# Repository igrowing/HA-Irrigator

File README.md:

# HA-Irrigator

## What is it?

An intuitive and human-friendly irrigation controller: 11 sprinkler zones + a shared pump, driven by a rotary-encoder + OLED local UI and a full MQTT API for Home Assistant integration. 

### Top differentiation points
- Human-friendly intuitive control on device and via Home Assistant.
- Flexible watering control — your command is never lost, your garden is never dry.
- Automatic watering adjustment based on the weather. Yes, it saves water when it rains!
- 110-240VAC pump control directly from the device, no extra contactors or relays.
- External antenna mount for placement wherever you want.
- Malfunction detection for the pump and valves: it protects your garden and your pocket from drying out.
- No battery! No chemical leaks, no device damage.
- Optional Home Assistant integration — works out of the box. It gives you:
  - Human-readable names for the irrigation zones.
  - Irrigation logging.
  - Remote control and status review.
  - Comfortable schedule building and editing.

## Why HA-Irrigator?

HA-Irrigator fixes the traditional shortcomings of industrial watering control systems.

| Trouble | Solution |
|---|---|
| 1.5V or 9V battery - the settings, the schedule, and the clock are backed up with regular batteries. You never know when the battery will die and leak into the device. And when the battery is dead and the mains power fails, you lose the whole schedule. This forces you to stand again in front of your irrigator, recall what the program was, and configure everything from scratch. | We keep all the settings and schedule in non-volatile memory. It does not require a battery. The clock runs on a battery that lasts 10 years and NEVER leaks. Your device is a safe investment, and your precious time is saved: no more re-configurations. |
| You cannot really manage any irrigator without reading manuals and standing in front of the device for a long time. | HA-Irrigator is intuitive! It requires zero configuration in front of the device. And when you approach it for manual commands, it helps you with on-screen hints. |
| Some irrigators have built-in or added Wi-Fi modules. But the Wi-Fi has a hidden antenna. This forces the owner to place the irrigator somewhere with decent Wi-Fi signal reception. | HA-Irrigator has an external SMA antenna connector. The owner is free to connect the antenna directly to the irrigator, or relocate it using a long enough coaxial cable to place the antenna in an area with good signal reception. |
| You never know if an industrial irrigator followed your program. You only find out once your garden dries up and dies. | HA-Irrigator gives you precise logging of what happened and when. |
| You must adjust the watering seasonally. If you forget, your garden suffers from lack of water, or your wallet suffers from excess spending. | HA-Irrigator has weather awareness. You just set a base watering amount per zone, and from there the system takes control: when it's too dry, watering is increased proportionally. When it rains, you save the water (and the cost). |
| Industrial irrigators force you to approach them and stand in front of the device to see its status or configure its programs. | We give you the power to see and change everything from your computer or mobile phone. More than that, it can be integrated with your smart home. So your home can configure the irrigator if you wish. |
| Traditionally, irrigators have at least 4 buttons and/or a dial with weird labels. Confusing and not intuitive. | This device has 1 (only one) knob. You rotate and push it like the volume knob in your car. And it helps you with navigation on the screen if you get lost. |
| Manual control of a normal irrigator is timed out. It takes your command after 10-30 seconds. | HA-Irrigator does not waste your time. Your command is executed immediately. If you don't appreciate half a minute of your life wasted, then this feature is meaningless :) |
| Usually, if you set a different manual command on a normal irrigator, the current watering is aborted. | HA-Irrigator assumes that every command is important. It puts all your commands in line. When the command's turn arrives, it is executed. Just fire and forget. |
| Industrial irrigators have a limit on programs, and a limit on entries per program. Why? | We hate limits. Feel free to build the weirdest schedule ever, we accommodate that! |
| Even if an off-the-shelf irrigator provides "smart" access and features, it only works if you're close to it (over Bluetooth) or over the vendor's remote server (forget your privacy!) | HA-Irrigator is your private system: you run it, access it as you want, configure it — you're in control! |

## Feature overview

- **11 independently-named sprinkler zones** plus pump-only runs, with the pump always
  pre-started ~500ms before a valve opens and kept on for a 60s graceful-shutdown window after a
  valve closes (protects the pump from rapid-cycle wear) — if another watering is queued up, it
  hands off to the still-running pump immediately instead of waiting out that window. Each zone
  can also be individually disabled (`settings.json`'s `zone_names.<n>.enabled`) to exclude it
  from scheduled, manual, and MQTT-triggered watering alike — an MQTT `cmd/run` against a disabled
  zone is rejected with a `/alert` instead of running, and the local UI's manual zone picker (see
  below) skips disabled zones entirely so they can't be dialed up in the first place.
- **Weekly schedule** (`schedule.json`, almost endless count of records) with a per-zone watering-percentage
  multiplier, a pause/rain-skip mechanism, and a 15-deep queue so overlapping or MQTT-triggered
  runs during an active watering don't get lost — they queue and run in order, back-to-back on
  the same pump cycle whenever the pump is still spinning down from the previous one.
- **Local UI**: 2.4-inch OLED display and knob, auto-dimming after 20s of inactivity, full menu for stopping, viewing/adjusting the schedule, and settings.
- **MQTT**: Key feature, allowing you to connect HA-Irrigator to practically any smart home system. Provides status/availability reporting (Home-Assistant-compatible LWT), remote run/stop/schedule control, current-fault alerting, OTA updates, calibration, and file backup.
- **Captive-portal setup**: first boot (or after a factory-reset-style config wipe) serves a
  Wi-Fi AP with a setup page; it tests both Wi-Fi *and* MQTT connectivity before committing the new config, and rolls back to AP mode if either fails.
- **DS3231-backed clock** with NTP sync, a timezone auto-detected from the device's location (no
  dropdown to pick), and automatic EU DST switching (last Sunday of March/October, 01:00 UTC).
- **Weather-based auto-adjustment**: once the device knows its location (auto-detected via
  ip-api.com, no setup needed), it fetches a forecast (Open-Meteo, with a WeatherAPI.com fallback)
  a few hours ahead of your first scheduled watering each day, skips the day's scheduled runs
  entirely when meaningful rain is forecast, and otherwise nudges the watering percentage up in
  hot weather / down after recent rain — all within a configurable lower/upper bound. See
  [docs/usage_irrigator.md](docs/usage_irrigator.md) and [docs/technical.md](docs/technical.md).
  The result of auto-adjustment work is shown on the chart below:

    * Rain reduces the waterin time/amount. The amount of rain in last 5 days has the same impact as forecasted amount of rain with probability higher than 70%.
    * You can adjust the probability of rain to be taken into account and the lower threshold to skip watering - default 40%.
- **Name your zones**. Numbers are nice, but words work better for people.
- Configurable time for testing of all zones.

## Device

## Screenshots

### Status and manual control

### Settings

### Schedule

See more screenshots in [User guide for HA](docs/usage_homeassistant.md).

## Useful (further reading)
- [User guide of the HA-Irrigator](docs/usage_irrigator.md), including installation instructions.
- [User-guide for HA integration](docs/integration.md).
- [User guide for HA](docs/usage_homeassistant.md).
- [Technical explanations](docs/technical.md) (for geeks only).
- [OTA firmware upgrade](docs/ota.md) (for makers only).
- [Crash dumps](docs/coredump.md) — retrieving and decoding a panic dump over MQTT (for makers only).
- [Hardware](hardware/readme.md).

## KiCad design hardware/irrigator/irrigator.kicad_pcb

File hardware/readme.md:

## Electronics

[Schematics](schematics.pdf)

ESP32 DevKit Pinout:

### Parts

| Ref             | Part                              | Description                                                                          | Qty |
|-----------------|------------------------------------|---------------------------------------------------------------------------------------|-----|
| U1              | ESP32-WROOM-32U dev kit           | Main microcontroller board                                                            | 1   |
| U2              | DS3231M                           | I2C real-time clock module                                                            | 1   |
| BT1             | CR2032                            | 3V coin cell, RTC backup battery                                                       | 1   |
| J6              | SSD1309 OLED 2.4"                     | I2C OLED display module                                                               | 1   |
| SW1             | Rotary encoder w/ push-button     | User input for menu navigation                                                         | 1   |
| U4              | AC-DC PSU, 230VAC → 5VDC 3A       | Powers ESP32, logic and display                                                        | 1   |
| —               | Transformer, 230VAC → 24VAC       | Powers valves relay coils (Eco wiring only)                                            | 1   |
| L1, L2          | HWCT-5A/5mV current clamp sensor  | Non-invasive AC current sensing — L1 on 24VAC (valves), L2 on 230VAC (pump)            | 2   |
| J1–J3           | 4-channel 5V relay module         | 12 relays total: 11 valves + 1 pump ("Relays group 1/2/3")                             | 3   |
| D1–D24          | 1N4003 diode                      | Only for non-opto-isolated ("red") relay modules; use a jumper instead on opto ("blue") modules | 24 (optional) |
| D25             | Blue LED, 5mm                     | Status/fault indicator                                                                | 1   |
| R1–R3, R8, R9, R12–R25 | 10kΩ resistor               | Pull-ups: rotary encoder, current sensors, relay inputs                               | 19  |
| R4, R5, R7, R11 | 100Ω resistor                     | Rotary encoder and current sensor signal conditioning                                  | 4   |
| R6, R10         | 1kΩ resistor                      | Current sensor burden resistor (24VAC / 230VAC)                                        | 2   |
| R26             | 30Ω resistor                      | LED current limiting                                                                   | 1   |
| C1, C4, C5      | 100nF capacitor                   | Rotary encoder debounce                                                                | 3   |
| C6, C7          | 10nF capacitor                    | Rotary encoder debounce                                                                | 2   |
| C2, C10         | 100µF 10V capacitor               | Decoupling (ESP32, OLED)                                                               | 2   |
| C8, C9          | 10µF 10V capacitor                | Current sensor filtering (24VAC / 230VAC)                                              | 2   |
| C3              | 470µF 16V capacitor               | PSU output smoothing                                                                   | 1   |
| J4, J5          | 19-pin headers                    | ESP32 devkit sockets                                                                   | 2   |
| J7–J9           | Screw terminal / JST connectors   | Mains AC in, PSU AC in, PSU DC out wiring                                              | 3   |

### About the relay modules
There are 2 types of "cheap" 4x relay modules on the market:

| PCB color | Blue | Red |
|--|--|--|
| Connectivity | 0.1" header | Terminal blocks |
| Active | Low | Configurable with jumper High/Low |
| Dimensions | Slightly larger | Slightly smaller |
| Optocopler | Less sensitive | Very sensitive |
| Assembly | simple | requires voltage drop diodes |

Red boards require volrage drop diodes to set the optocouplers in high state (non-active) when the MCU is high. All boards require pullups.

## Mechanical design

- [Base](irrigator%20box.stl)
- [Lid](irrigator%20lid.stl)

## Installation wiring

In industrial irrigators the 24VAC transformer is often integrated into the irrigator. This reduces the customer flexibility where to mount the irrigator and what type of valves to use. Also, always connected transformer has parasitic current consumptions which hits customer wallet and hurts to the ecology. Our irrigator allows using any 24VAC transformer. It can be mounted on DIN rail or standalone. And it can be driven together with pump, i.e. it is not always connected to mains. This means **more flexibility, less electricilty bill, and less environment impact**.

## Antenna

Wi-Fi reception is critical only for automatic watering adjustment by the weather and for Home Assistant integration. HA-Irrigator can work without Wi-Fi too.

However, for the sake of installation flexibility, the antenna has separate SMA connector. This allows to install the irrigator practically in any place and run the low-attentuating coaxial cable (type of LMR-240 or HF-240) for up to 10 meters. The antenna then, can be placed in the area with good Wi-Fi signal when the irrigator itself can be even in concrete bunker.

### Simple

### Eco

## Current sensing

There are only 2 current sensors in the irrigator:
- For the pump, 220-240VAC, high current up to 12A.
- For valves, 24VAC, sub-amper current, typically 250mA.

The current measurement is not mandatory for the irrigator functionality. However, it can be useful to detect overcurrent and under current events:
- Overcurrent:
  - Pump blocked.
  - Valve wiring short circuit.
- Undercurrent: circuit discontinuity resulting non-fucntioning pump and/or valve.

In both cases there is a risk of over-drying of your garden.

One valve current sensor is enough for 11 valves because valves are never opened together, only 1 zone works at every given moment. So it is easy to correlate which valve is malfunctioning.

The current sensing becomes functional only after [current sensor calibration](../docs/usage_irrigator.md#current-sensor-calibration-explained).

### Current sensor sensitivty

The schematics is built to provide the follwing current sensitivity:
| Sensor  | Sensitivity, mV/mA | Sensitivity, mV/A | Saturation (ceiling), A |
|--|--|--|--|
| Valve | 0.82 | 820 | 1.4 |
| Pump | 0.047| 47 | 24.5 |

This means, having `CURRENT_CALIBRATION_MIN_BASE_LEVEL = 30` will fail the calibration of valve which consumes less than 36 mA and the pump that draws less than 640 mA.

## Water flow sensing

### Flow meter: TUF-2000M

An ultrasonic clamp-on flow meter — no pipe-cutting install, reads flow rate and totalized volume over Modbus RTU on RS-485. It also carries its own onboard relay (OCT), configurable locally on the meter to trip on a flow-rate or totalizer threshold — that relay is meant to drive the shut-off valve directly as a hardware failsafe (see below), independent of the ESP32/Wi-Fi being alive.

### Flow meter settings (set on the meter's keypad)

The firmware talks Modbus RTU to slave 1 at 9600 8N1 (see `FLOW_METER_*` in [board_config.h](../include/board_config.h)). The meter must be configured to match, or it stays silent and every request times out (`/cmd/meter` shows `"error": "no valid reading yet"` with `last_modbus_error_text: "Timeout"`).

| Menu | Setting | Required value | Note |
|--|--|--|--|
| M11 | Pipe outer diameter | 44 | Measure yours |
| M12 | Pipe thickness | 9 | Measure yours |
| M14 | Pipe material | 9 (other)| For plastic green pipes |
| M15 | Sound speed in pipe material | 2650 | Not needed to change is non-"other" known pipe material is used |
| M16 | Pipe liner | No Liner | Or select needed liner |
| M18 | Pipe inner diameter |  | Just see that meter calculated your pipe correctly, having pipe OD and thickness (M11, M12) |
| M20 | Liquid type | 0 (water) |  |
| M23 | Transducer type | 19 (TS-2) | Choose your transducer type |
| M24 | Transducer mounting | V or W | Choose what suits better your pipe. For very small pipes W works better. For 1" and up OD the V is good enough |
| M25 | Distance between transducers |  | See for easy of adjustment |
| M63 | Communication protocol | **MODBUS RTU** | Factory default is MODBUS ASCII, which ignores RTU frames completely. Forgetting this was the cause of the first bring-up timeout. |
| M62 | RS-232/RS-485 setup | 9600 baud, parity none, 8 data bits, 1 stop bit | Factory default. Any other parity makes the meter drop every frame silently. |
| M46 | Network address (ID) | 1 | Must equal `FLOW_METER_MODBUS_SLAVE_ID`. |
| M26 | Save settings (Solidify) | run after changing the above | Settings live in RAM until stored. Without this step they revert on the next power cycle (manual, page 4). |

#### Placing and adjustment of transducers
1. Decide the water direction. Put the "Up" transducer on a side from where the water runs. Put the "Down" transducer on a side where the water runs.
2. Use provided with the meter silicon-like tighthening cream between the transducer and the pipe to make air-less tight placement.
3. Using menu M90 move the transducers slightly around the calculated distance from M25 to read on the display Q value between 60 and 90. More is better. After every slight position change let the meter 3-5 seconds to show you the new Q value. When you reached best possible Q, tighten the transducers with provided rings.

#### Diagnosing a silent bus
Menu M49 on the meter displays the raw bytes it receives on the serial port. If bytes show up every couple of seconds, wiring and converter are fine and the fault is in M63/M62/M46. If M49 stays empty, look at the physical link (A/B, termination, converter). On the converter, the R LED blinks for each request coming from the ESP32 and the T LED blinks for each reply going back to it.

#### Meter adjustment
Meter might count water flow even on still water. And it may count the flow wrongly.

1. To set 0 liquid flow, use menu M42. Activating it, wait 30 seconds: do not touch the meter and make 100% sure the water is NOT running.
2. To calibrate the water flow measurement use menu M45. The scale factor is expected/actual.

### RS-485 GPIOs

Every strapping-safe, output-capable GPIO is already claimed by zones/pump/LED/rotary/ADC/I2C (see [board_config.h](../include/board_config.h)), and GPIO0/1/3 are off-limits (factory-reset button, and `Serial`/flashing). That leaves only GPIO2 and GPIO12 — both ESP32 boot-strapping pins:

| Signal | PIN |
|--|--|
| ESP32 TX → converter RXD | 2 | 
| ESP32 RX ← converter TXD | 36 | 
| DE/RE | — (unused/automatic) | 
| GND | GND | 
| VIN | 3V3 |

### RS-485 converter: Waveshare TTL TO RS485 (C)

Picked over a plain MAX485-style breakout for two reasons:
- **Galvanic isolation.** This cable run parallels mains wiring through the garage; the module isolates the RS-485 bus side (both power and signal, via an onboard isolated DC-DC plus a digital isolator) from the ESP32's own logic and ground, so an induced spike on the bus has no metallic path to the MCU even if it gets past the onboard TVS clamp first.
- **Automatic direction switching**, built into the chip — no DE/RE control needed, so the link only spends the 2 GPIOs above instead of 3.

Also has onboard 120Ω termination (enabled by soldering a jumper) and 200W surge / 6kV ESD protection on the bus side. TTL-side pinout: VCC / TXD / RXD / GND, wired to the ESP32's 3.3V / GPIO36 / GPIO2 / GND (crossed: the converter's RXD receives what the ESP32 transmits on GPIO2, and its TXD feeds GPIO36); RS-485 side: A+ / B- / PE.

### Wiring the RS-485 cable

- Shielded twisted pair for A/B.
- Land the shield on the converter's **PE** terminal, at the ESP32 end only — don't also ground it at the flow meter end (that turns the shield into a ground-loop path), and don't bridge PE to the TTL-side GND (that defeats the isolation).
- No common GND wire: the meter's RS-485 port is itself isolated, and its GND terminal is only the transducer ground ("NOT for power and AO and RS485", manual page 8). Two isolated ports need only the A/B pair; this link works that way.

### Why the 120Ω terminator matters

RS-485 is a shared differential line; an un-terminated cable end reflects a fast signal edge back down the wire instead of absorbing it, corrupting bytes — worse at higher baud rates or longer runs. A 120Ω resistor at each of the two *physical ends* of the bus (matched to the cable's characteristic impedance) soaks up the edge instead of reflecting it. Enable it only at the two endpoints, never at an intermediate device on a multi-drop run — extra resistors along the way just overload the driver and attenuate the signal for everyone.

### Room for more RS-485 devices later

RS-485/Modbus is multi-drop: a shut-off valve controller or any other Modbus RTU device can join the same A/B pair later with its own slave ID — no extra ESP32 pins or a second converter needed, they all share this one bus.

### Shut-off valve strategy

Prefer the TUF-2000M's own relay, configured locally (flow-rate or totalizer threshold), as the failsafe that closes a master shut-off valve even when the ESP32 or Wi-Fi is down — the same "don't trust the network for safety-critical stuff" principle the current-sensing overcurrent checks already follow. Poll flow readings over Modbus in firmware as well, for HA reporting/logging and for schedule-aware logic the meter alone can't know (e.g. unusually high volume mid-cycle for whichever zone is currently running).

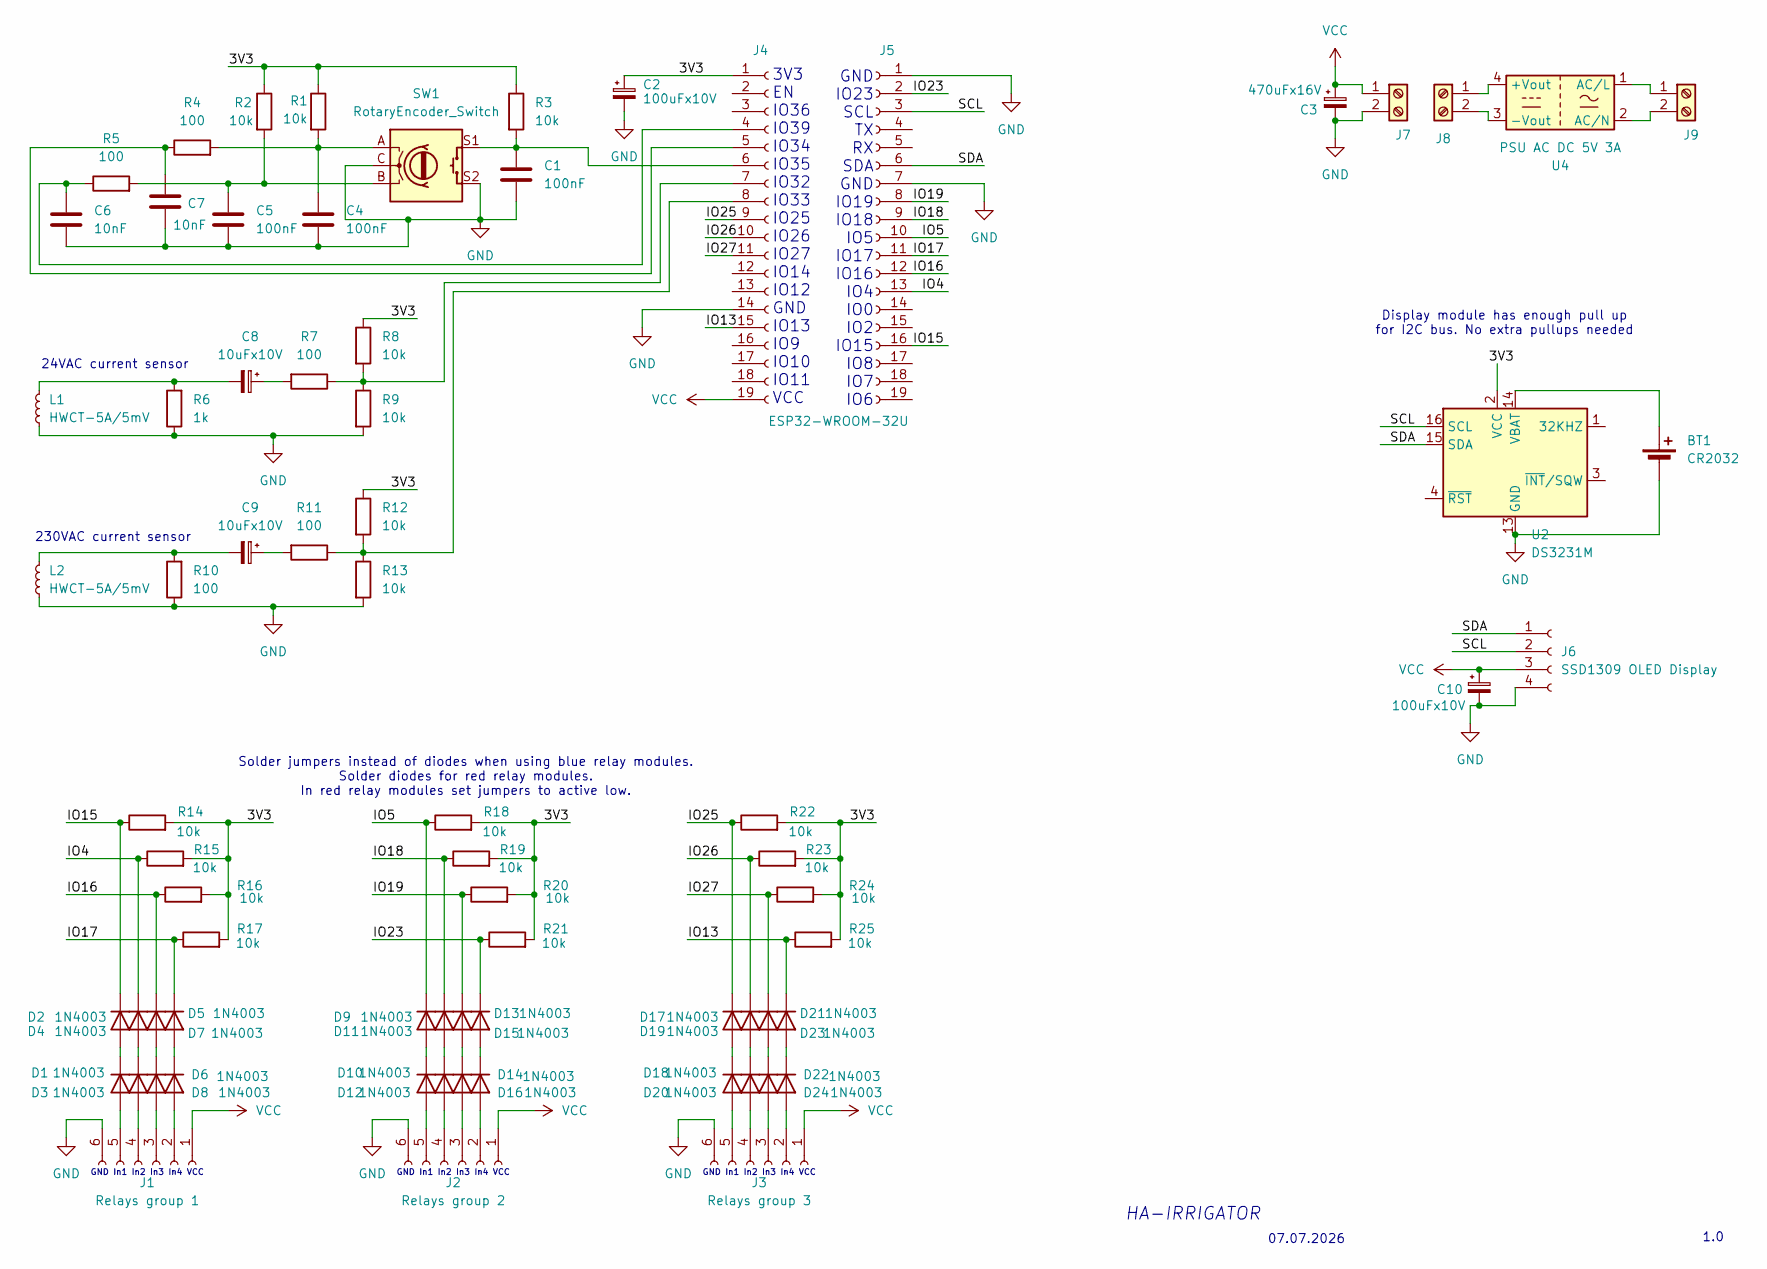
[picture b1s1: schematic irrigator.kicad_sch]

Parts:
BT1: CR2032; BatteryHolder_Keystone_3002_1x2032
C1, C4, C5: 100nF; C_0603_1608Metric
C2, C10: 100uFx10V; CP_EIA-1608-10_AVX-L
C3: 470uFx16V; C_1808_4520Metric
C6, C7: 10nF; C_0603_1608Metric
C8, C9: 10uFx10V; C_0805_2012Metric
D1, D2, D3, D4, D5, D6, D7, D8, D9, D10, D11, D12, D13, D14, D15, D16, D17, D18, D19, D20, D21, D22, D23, D24: 1N4003; D_DO-41_SOD81_P10.16mm_Horizontal
J1: Relays group 1; PinHeader_1x06_P2.54mm_Vertical
J2: Relays group 2; PinHeader_1x06_P2.54mm_Vertical
J3: Relays group 3; PinHeader_1x06_P2.54mm_Vertical
J4: PinHeader_1x19_P2.54mm_Vertical
J5: ESP32-WROOM-32U; PinHeader_1x19_P2.54mm_Vertical
J6: SSD1309 OLED Display; PinHeader_1x04_P2.54mm_Vertical
J7, J8, J9: TerminalBlock_MaiXu_MX126-5.0-02P_1x02_P5.00mm
L1, L2: HWCT-5A/5mV; L_Axial_L12.0mm_D5.0mm_P15.24mm_Horizontal_Fastron_MISC
R1, R2, R3, R8, R9, R12, R13, R14, R15, R16, R17, R18, R19, R20, R21, R22, R23, R24, R25: 10k; R_0603_1608Metric
R4, R5, R7, R10, R11: 100; R_0603_1608Metric
R6: 1k; R_0603_1608Metric
SW1: RotaryEncoder_Switch; RotaryEncoder_Alps_EC11E-Switch_Vertical_H20mm
U2: DS3231M; SOIC-16W_7.5x10.3mm_P1.27mm
U4: PSU AC DC 5V 3A; Converter_ACDC_Hi-Link_HLK-20Mxx

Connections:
/3V3: C2.1, J4.1, R1.1, R2.1, R3.1, R8.1, R12.1, R14.2, R15.2, R16.2, R17.2, R18.2, R19.2, R20.2, R21.2, R22.2, R23.2, R24.2, R25.2
/IO4: D4.1 (K), J5.13, R15.1
/IO5: D9.1 (K), J5.10, R18.1
/IO13: D23.1 (K), J4.15, R25.1
/IO15: D2.1 (K), J5.16, R14.1
/IO16: D5.1 (K), J5.12, R16.1
/IO17: D7.1 (K), J5.11, R17.1
/IO18: D11.1 (K), J5.9, R19.1
/IO19: D13.1 (K), J5.8, R20.1
/IO23: D15.1 (K), J5.2, R21.1
/IO25: D17.1 (K), J4.9, R22.1
/IO26: D19.1 (K), J4.10, R23.1
/IO27: D21.1 (K), J4.11, R24.1
/SCL: J5.3, J6.2, U2.16 (SCL)
/SDA: J5.6, J6.1, U2.15 (SDA)
GND: BT1.2 (-), C1.2, C2.2, C3.2, C4.2, C5.2, C6.2, C7.2, C10.2, J1.6, J2.6, J3.6, J4.14, J5.1, J5.7, J6.4, J7.2, L1.1, L2.1, R6.1, R9.2, R10.1, R13.2, SW1.C, SW1.S2, U2.5 (GND), U2.6 (GND), U2.7 (GND), U2.8 (GND), U2.9 (GND), U2.10 (GND), U2.11 (GND), U2.12 (GND), U2.13 (GND)
unnamed: BT1.1 (+), U2.14 (VBAT)
unnamed: C4.1, R1.2, R4.2, SW1.A
unnamed: C5.1, R2.2, R5.2, SW1.B
unnamed: C8.1, R7.2
unnamed: C8.2, L1.2, R6.2
unnamed: C9.1, R11.2
unnamed: C9.2, L2.2, R10.2
unnamed: D1.2 (A), J1.5
unnamed: D1.1 (K), D2.2 (A)
unnamed: D3.2 (A), J1.4
unnamed: D3.1 (K), D4.2 (A)
unnamed: D5.2 (A), D6.1 (K)
unnamed: D6.2 (A), J1.3
unnamed: D7.2 (A), D8.1 (K)
unnamed: D8.2 (A), J1.2
unnamed: D10.2 (A), J2.5
unnamed: D9.2 (A), D10.1 (K)
unnamed: D11.2 (A), D12.1 (K)
unnamed: D12.2 (A), J2.4
unnamed: D13.2 (A), D14.1 (K)
unnamed: D14.2 (A), J2.3
unnamed: D15.2 (A), D16.1 (K)
unnamed: D16.2 (A), J2.2
unnamed: D17.2 (A), D18.1 (K)
unnamed: D18.2 (A), J3.5
unnamed: D19.2 (A), D20.1 (K)
unnamed: D20.2 (A), J3.4
unnamed: D21.2 (A), D22.1 (K)
unnamed: D22.2 (A), J3.3
unnamed: D23.2 (A), D24.1 (K)
unnamed: D24.2 (A), J3.2
unnamed: C6.1, J4.4, R5.1
unnamed: C7.1, J4.5, R4.1
unnamed: C1.1, J4.6, R3.2, SW1.S1
unnamed: J4.7, R7.1, R8.2, R9.1
unnamed: J4.8, R11.1, R12.2, R13.1
unnamed: J8.1, U4.4 (+Vout)
unnamed: J8.2, U4.3 (-Vout)
unnamed: J9.1, U4.1 (AC/L)
unnamed: J9.2, U4.2 (AC/N)
VCC: C3.1, C10.1, J1.1, J2.1, J3.1, J4.19, J6.3, J7.1

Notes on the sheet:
GND In1 In2 In3 In4 VCC
1.0
Display module has enough pull up for I2C bus. No extra pullups needed
230VAC current sensor
Solder jumpers instead of diodes when using blue relay modules. Solder diodes for red relay modules. In red relay modules set jumpers to active low.
GND IO23 SCL TX RX SDA GND IO19 IO18 IO5 IO17 IO16 IO4 IO0 IO2 IO15 IO8 IO7 IO6
3V3 EN IO36 IO39 IO34 IO35 IO32 IO33 IO25 IO26 IO27 IO14 IO12 GND IO13 IO9 IO10 IO11 VCC
24VAC current sensor
HA-IRRIGATOR
07.07.2026

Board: 2 copper layers, 74 parts (0 on the bottom side), 57 nets, no tracks yet.
